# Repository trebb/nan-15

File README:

NaN-15 -- a 15-key DIY computer keyboard

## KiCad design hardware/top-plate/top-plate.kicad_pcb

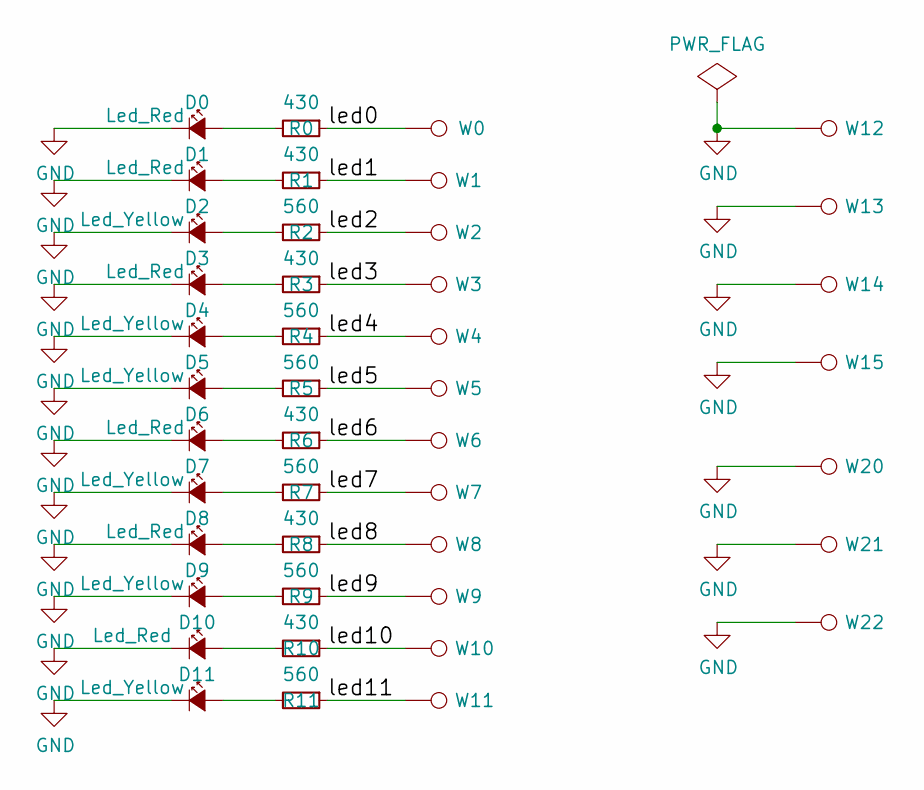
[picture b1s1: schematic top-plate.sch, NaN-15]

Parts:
D0, D1, D3, D6, D8, D10: Led_Red; LED_1206_REVERSE
D2, D4, D5, D7, D9, D11: Led_Yellow; LED_1206_REVERSE
R0, R1, R3, R6, R8, R10: 430; R_1206
R2, R4, R5, R7, R9, R11: 560; R_1206
W0, W1, W2, W3, W4, W5, W6, W7, W8, W9, W10, W11, W12, W13, W14, W15: TEST_1P; SolderWirePad_2mm_1-2mmDrill_no_legend
W20, W21, W22: TEST_1P; MountingHole_2.2mm_M2_Pad

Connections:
/led0: R0.1, W0.1
/led1: R1.1, W1.1
/led2: R2.1, W2.1
/led3: R3.1, W3.1
/led4: R4.1, W4.1
/led5: R5.1, W5.1
/led6: R6.1, W6.1
/led7: R7.1, W7.1
/led8: R8.1, W8.1
/led9: R9.1, W9.1
/led10: R10.1, W10.1
/led11: R11.1, W11.1
GND: D0.1 (K), D1.1 (K), D2.1 (K), D3.1 (K), D4.1 (K), D5.1 (K), D6.1 (K), D7.1 (K), D8.1 (K), D9.1 (K), D10.1 (K), D11.1 (K), W12.1, W13.1, W14.1, W15.1, W20.1, W21.1, W22.1
unnamed: D0.2 (A), R0.2
unnamed: D1.2 (A), R1.2
unnamed: D2.2 (A), R2.2
unnamed: D3.2 (A), R3.2
unnamed: D4.2 (A), R4.2
unnamed: D5.2 (A), R5.2
unnamed: D6.2 (A), R6.2
unnamed: D7.2 (A), R7.2
unnamed: D8.2 (A), R8.2
unnamed: D9.2 (A), R9.2
unnamed: D10.2 (A), R10.2
unnamed: D11.2 (A), R11.2

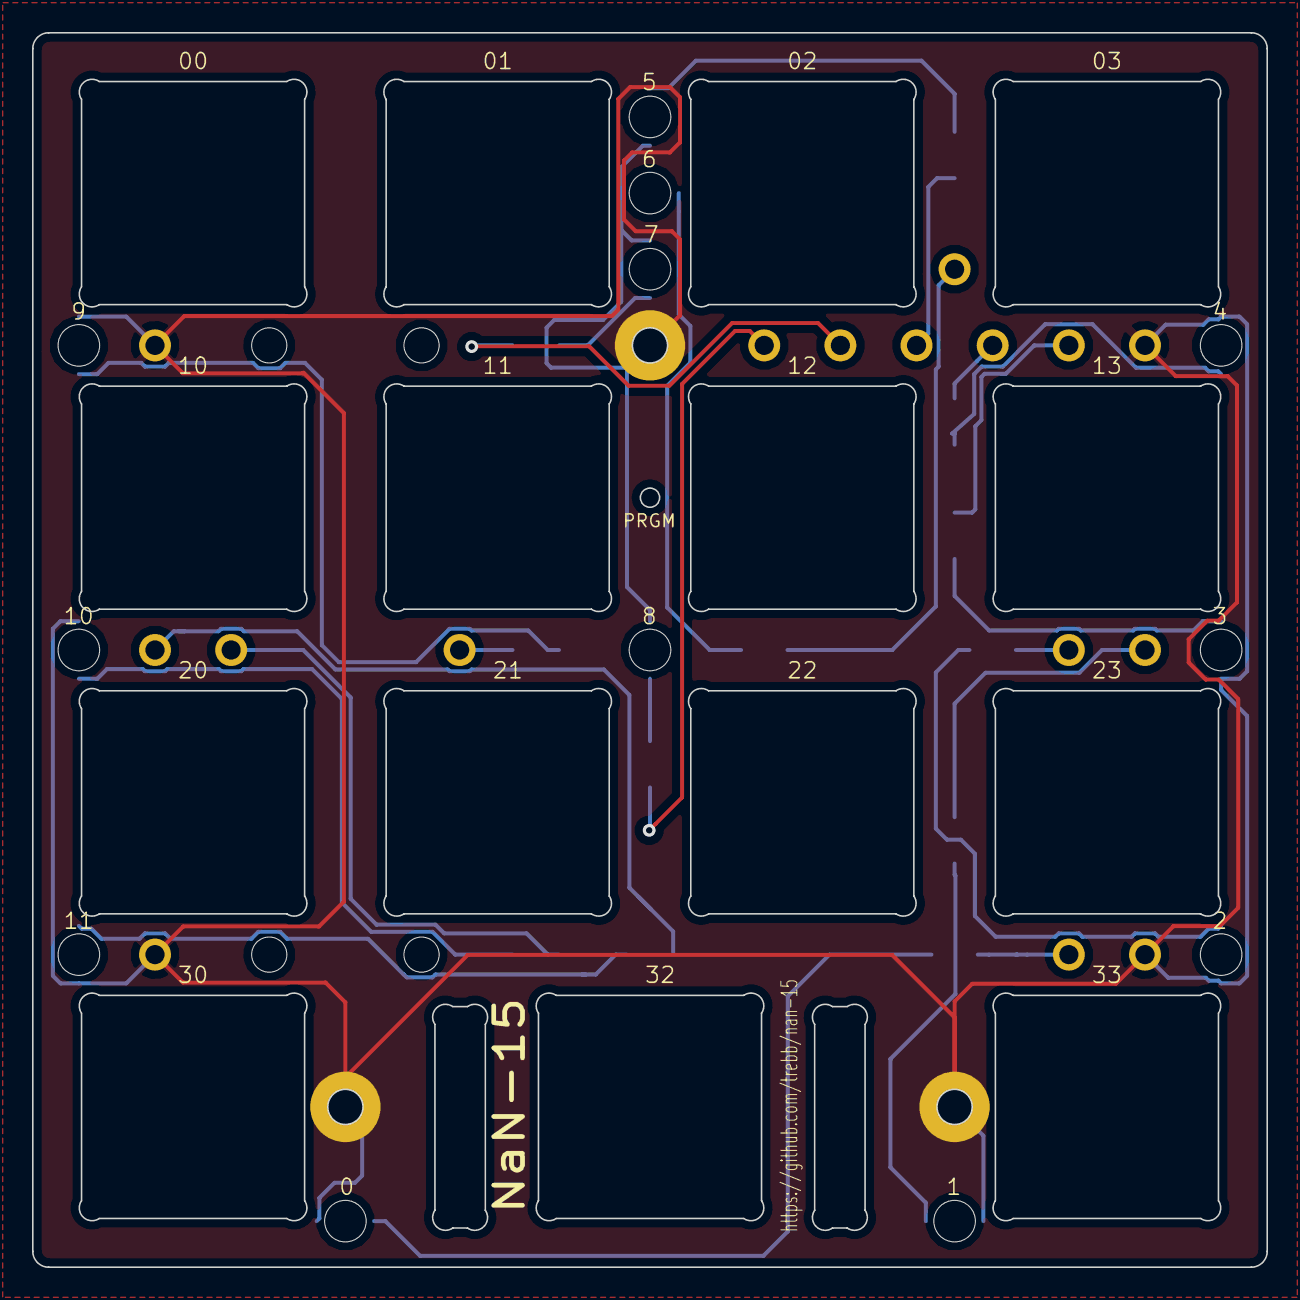
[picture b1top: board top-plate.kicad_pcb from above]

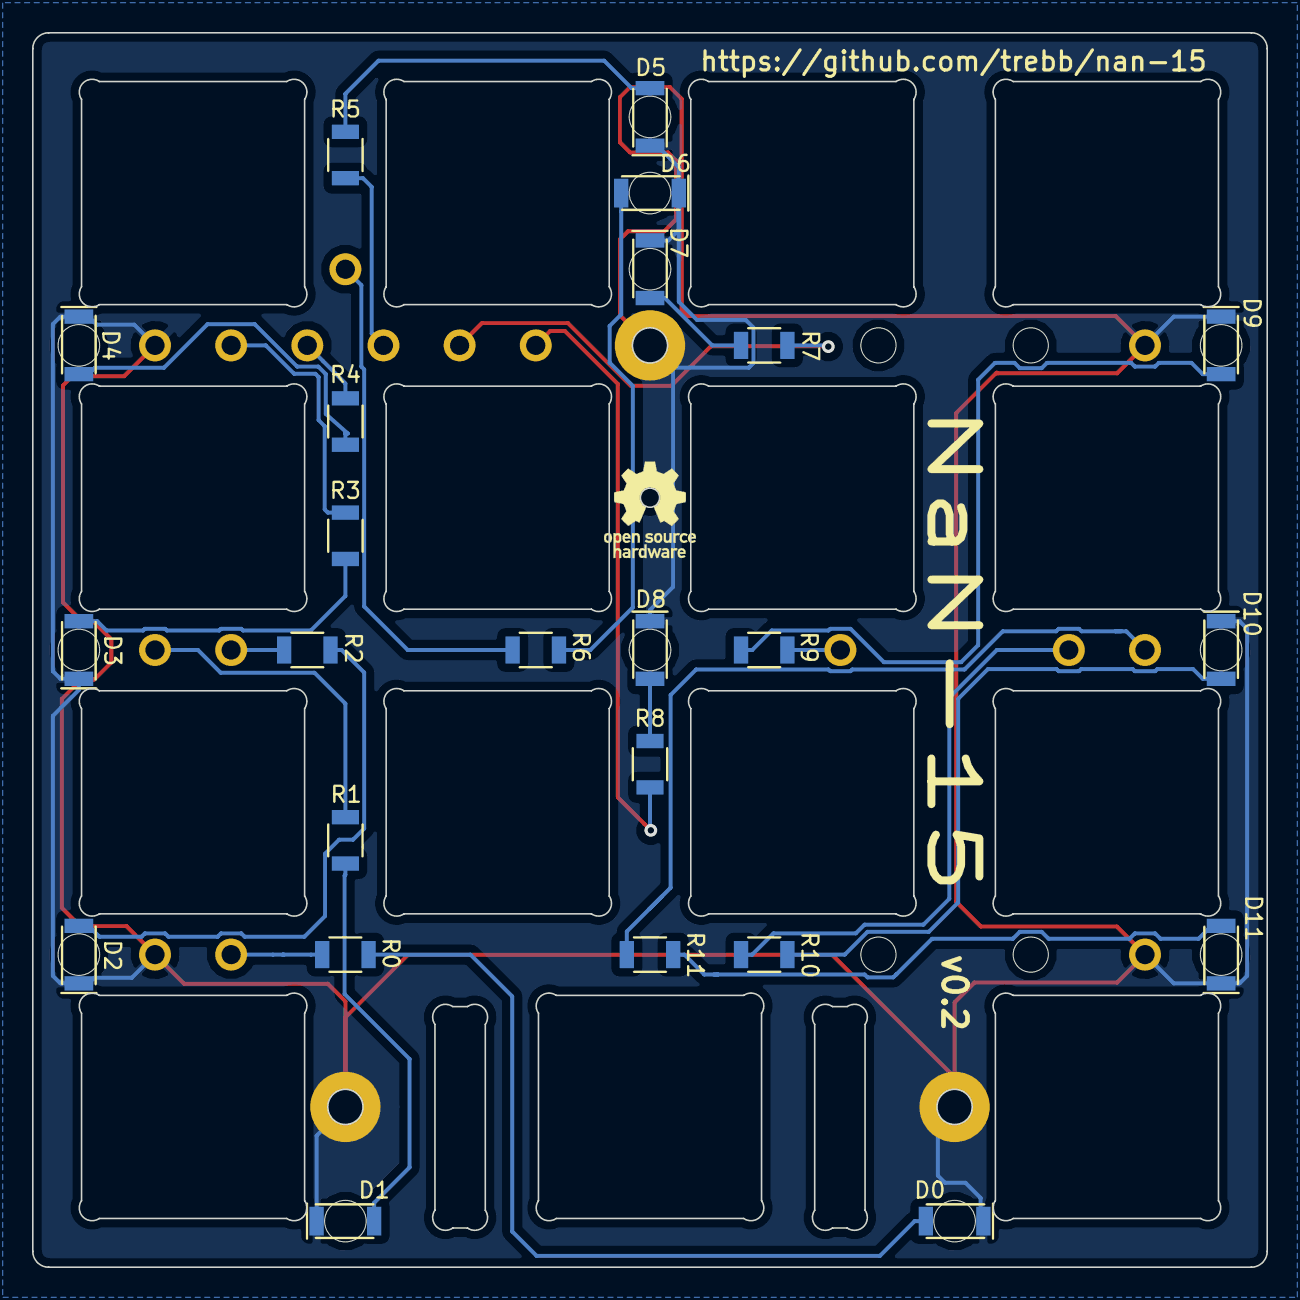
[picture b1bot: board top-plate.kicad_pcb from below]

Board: 2 copper layers, 77.2 x 77.2 mm, 47 parts (24 on the bottom side), 25 nets.

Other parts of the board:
HS4, HS5, HS6, HS7: HEATSINK; MountingHole_2.2mm_M2

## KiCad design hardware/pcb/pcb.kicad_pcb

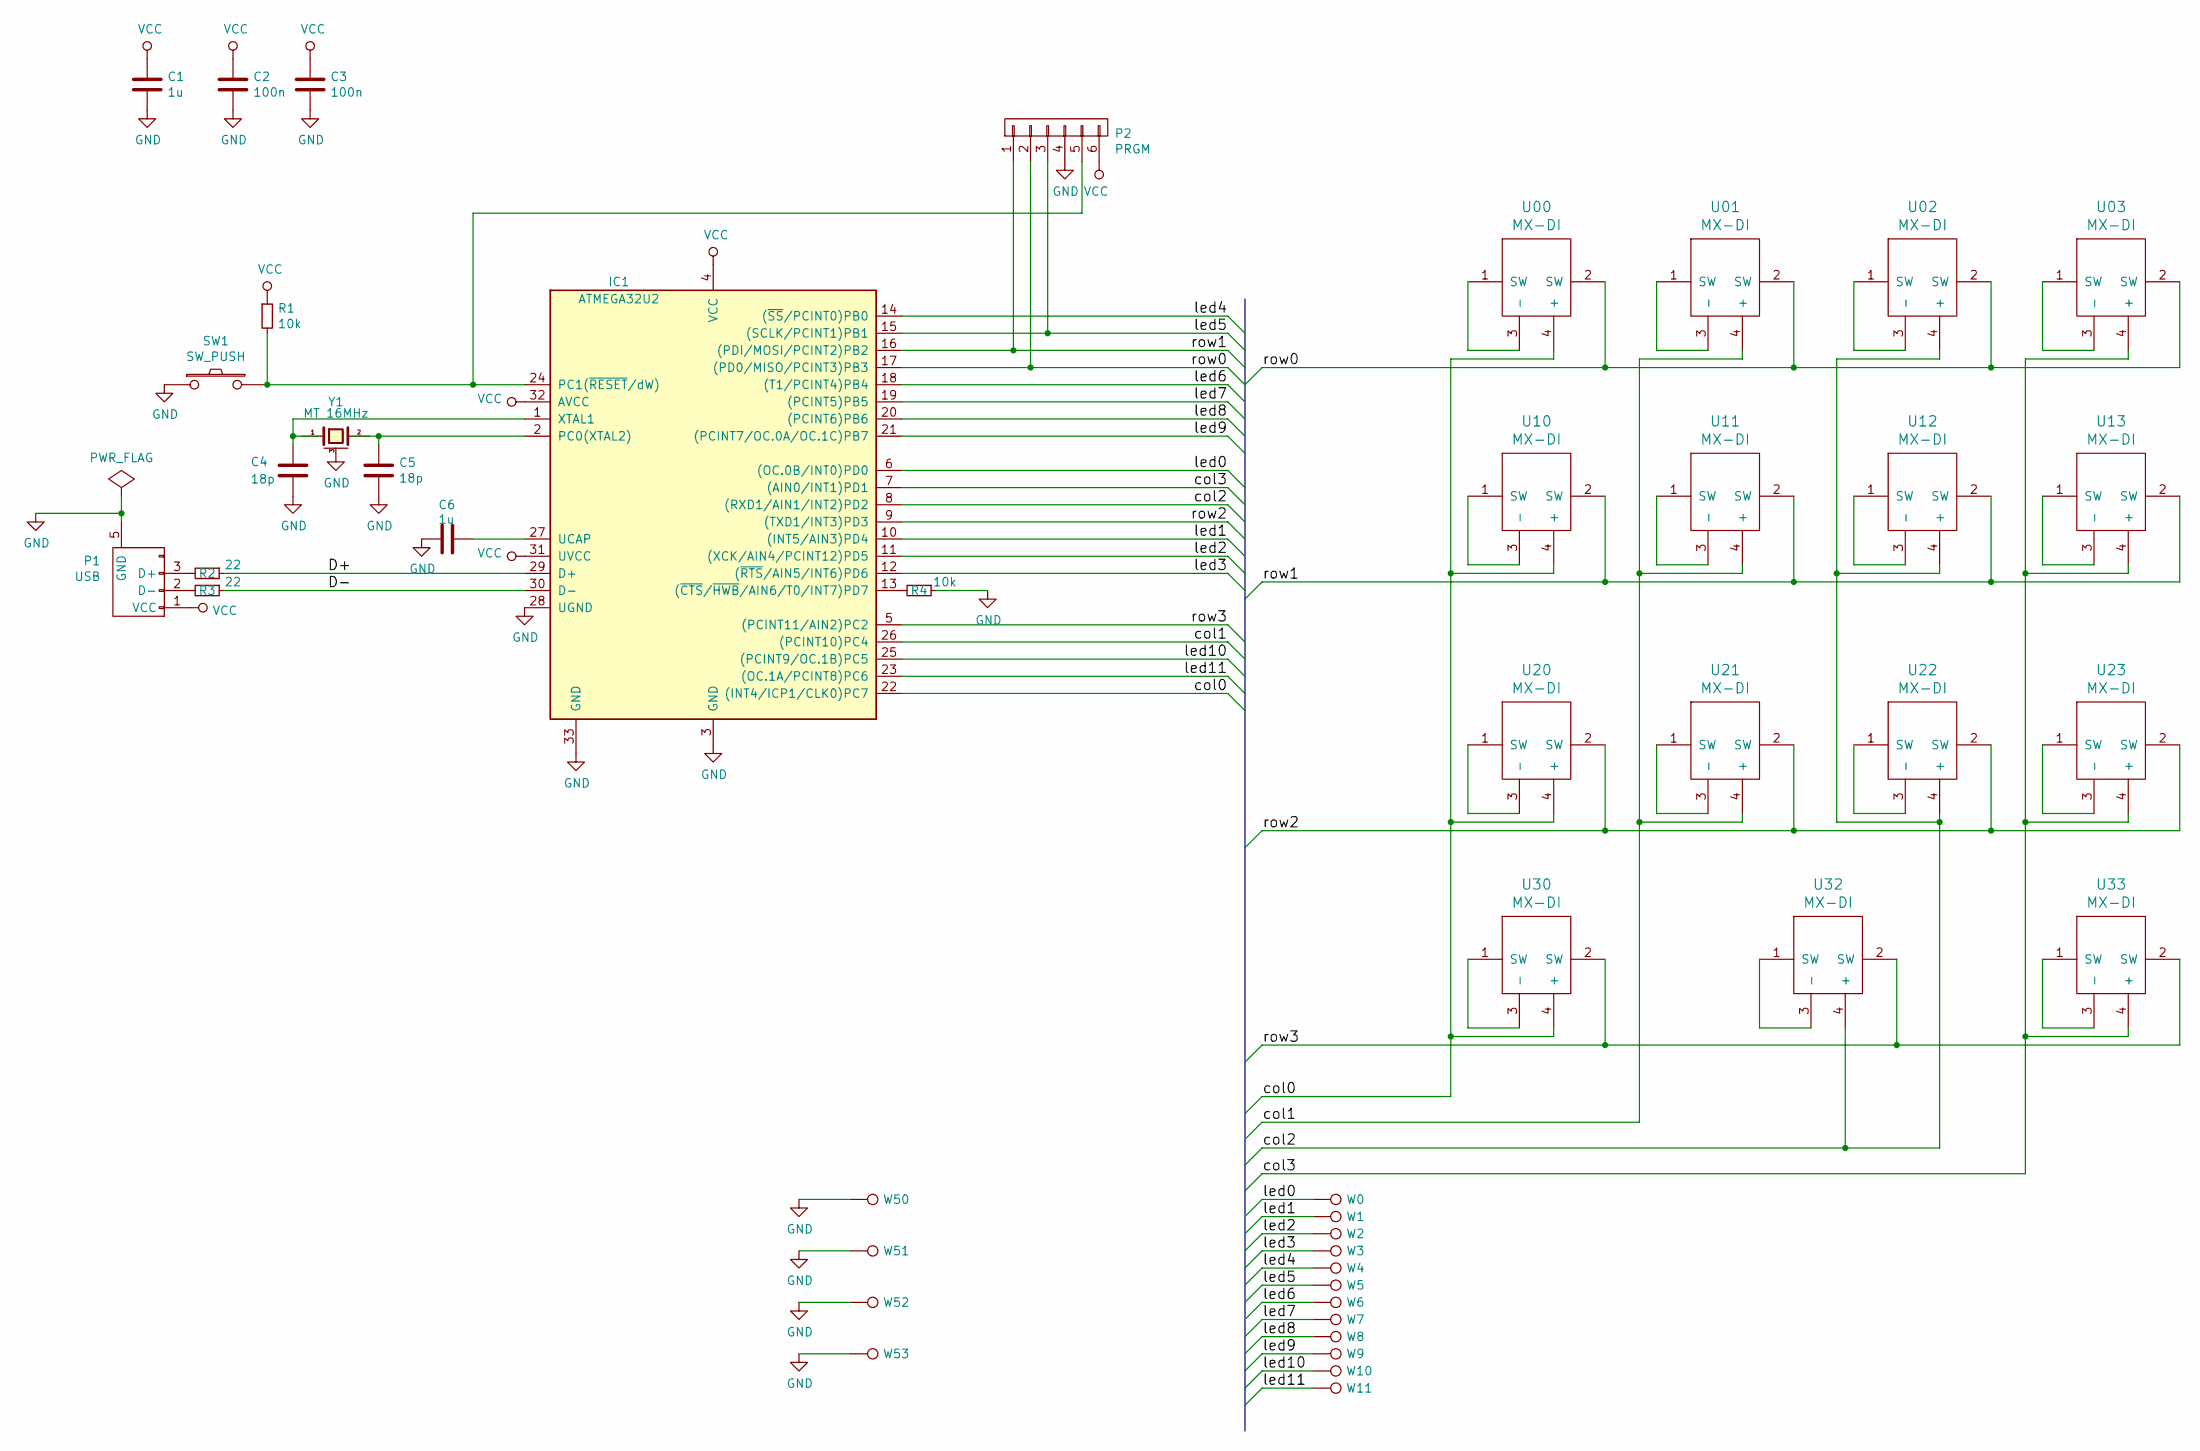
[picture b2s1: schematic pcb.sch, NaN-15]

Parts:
C1, C6: 1u; C_1206
C2, C3: 100n; C_1206
C4, C5: 18p; C_1206
IC1: ATMEGA32U2; QFN-32-1EP_5x5mm_Pitch0.5mm
P1: USB; SolderWirePad_4xInline_1mmDrill
P2: PRGM; Program_1x06
R1, R4: 10k; R_1206
R2, R3: 22; R_1206
SW1: SW_PUSH; button_3x6_smd
U00, U01, U02, U03, U10, U11, U12, U13, U20, U21, U22, U23, U30, U32, U33: MX-DI; MXDIODE
W0, W1, W2, W3, W4, W5, W6, W7, W8, W9, W10, W11, W50, W51, W52, W53: TEST_1P; SolderWirePad_2mm_1-2mmDrill_no_legend
Y1: MT 16MHz; crystal_MT_32x25

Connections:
/D+: IC1.29 (D+), R2.1
/D-: IC1.30 (D-), R3.1
/col0: IC1.22 ((INT4/ICP1/CLK0)PC7), U00.4 (+), U10.4 (+), U20.4 (+), U30.4 (+)
/col1: IC1.26 ((PCINT10)PC4), U01.4 (+), U11.4 (+), U21.4 (+)
/col2: IC1.8 ((RXD1/AIN1/INT2)PD2), U02.4 (+), U12.4 (+), U22.4 (+), U32.4 (+)
/col3: IC1.7 ((AIN0/INT1)PD1), U03.4 (+), U13.4 (+), U23.4 (+), U33.4 (+)
/led0: IC1.6 ((OC.0B/INT0)PD0), W0.1
/led1: IC1.10 ((INT5/AIN3)PD4), W1.1
/led2: IC1.11 ((XCK/AIN4/PCINT12)PD5), W2.1
/led3: IC1.12 ((~RTS~/AIN5/INT6)PD6), W3.1
/led4: IC1.14 ((~SS~/PCINT0)PB0), W4.1
/led5: IC1.15 ((SCLK/PCINT1)PB1), P2.3, W5.1
/led6: IC1.18 ((T1/PCINT4)PB4), W6.1
/led7: IC1.19 ((PCINT5)PB5), W7.1
/led8: IC1.20 ((PCINT6)PB6), W8.1
/led9: IC1.21 ((PCINT7/OC.0A/OC.1C)PB7), W9.1
/led10: IC1.25 ((PCINT9/OC.1B)PC5), W10.1
/led11: IC1.23 ((OC.1A/PCINT8)PC6), W11.1
/row0: IC1.17 ((PD0/MISO/PCINT3)PB3), P2.2, U00.2 (SW), U01.2 (SW), U02.2 (SW), U03.2 (SW)
/row1: IC1.16 ((PDI/MOSI/PCINT2)PB2), P2.1, U10.2 (SW), U11.2 (SW), U12.2 (SW), U13.2 (SW)
/row2: IC1.9 ((TXD1/INT3)PD3), U20.2 (SW), U21.2 (SW), U22.2 (SW), U23.2 (SW)
/row3: IC1.5 ((PCINT11/AIN2)PC2), U30.2 (SW), U32.2 (SW), U33.2 (SW)
GND: C1.2, C2.2, C3.2, C4.2, C5.2, C6.1, IC1.3 (GND), IC1.28 (UGND), IC1.33 (GND), P1.5 (GND), P2.4, R4.1, SW1.1, W50.1, W51.1, W52.1, W53.1, Y1.3 (case)
unnamed: C4.1, IC1.1 (XTAL1)
unnamed: C5.1, IC1.2 (PC0(XTAL2))
unnamed: C6.2, IC1.27 (UCAP)
unnamed: IC1.13 ((~CTS~/~HWB~/AIN6/T0/INT7)PD7), R4.2
unnamed: IC1.24 (PC1(~RESET~/dW)), P2.5, R1.2, SW1.2
unnamed: P1.2 (D-), R3.2
unnamed: P1.3 (D+), R2.2
unnamed: U00.1 (SW), U00.3 (-)
unnamed: U01.1 (SW), U01.3 (-)
unnamed: U02.1 (SW), U02.3 (-)
unnamed: U03.1 (SW), U03.3 (-)
unnamed: U10.1 (SW), U10.3 (-)
unnamed: U11.1 (SW), U11.3 (-)
unnamed: U12.1 (SW), U12.3 (-)
unnamed: U13.1 (SW), U13.3 (-)
unnamed: U20.1 (SW), U20.3 (-)
unnamed: U21.1 (SW), U21.3 (-)
unnamed: U22.1 (SW), U22.3 (-)
unnamed: U23.1 (SW), U23.3 (-)
unnamed: U30.1 (SW), U30.3 (-)
unnamed: U32.1 (SW), U32.3 (-)
unnamed: U33.1 (SW), U33.3 (-)
VCC: C1.1, C2.1, C3.1, IC1.4 (VCC), IC1.31 (UVCC), IC1.32 (AVCC), P1.1 (VCC), P2.6, R1.1

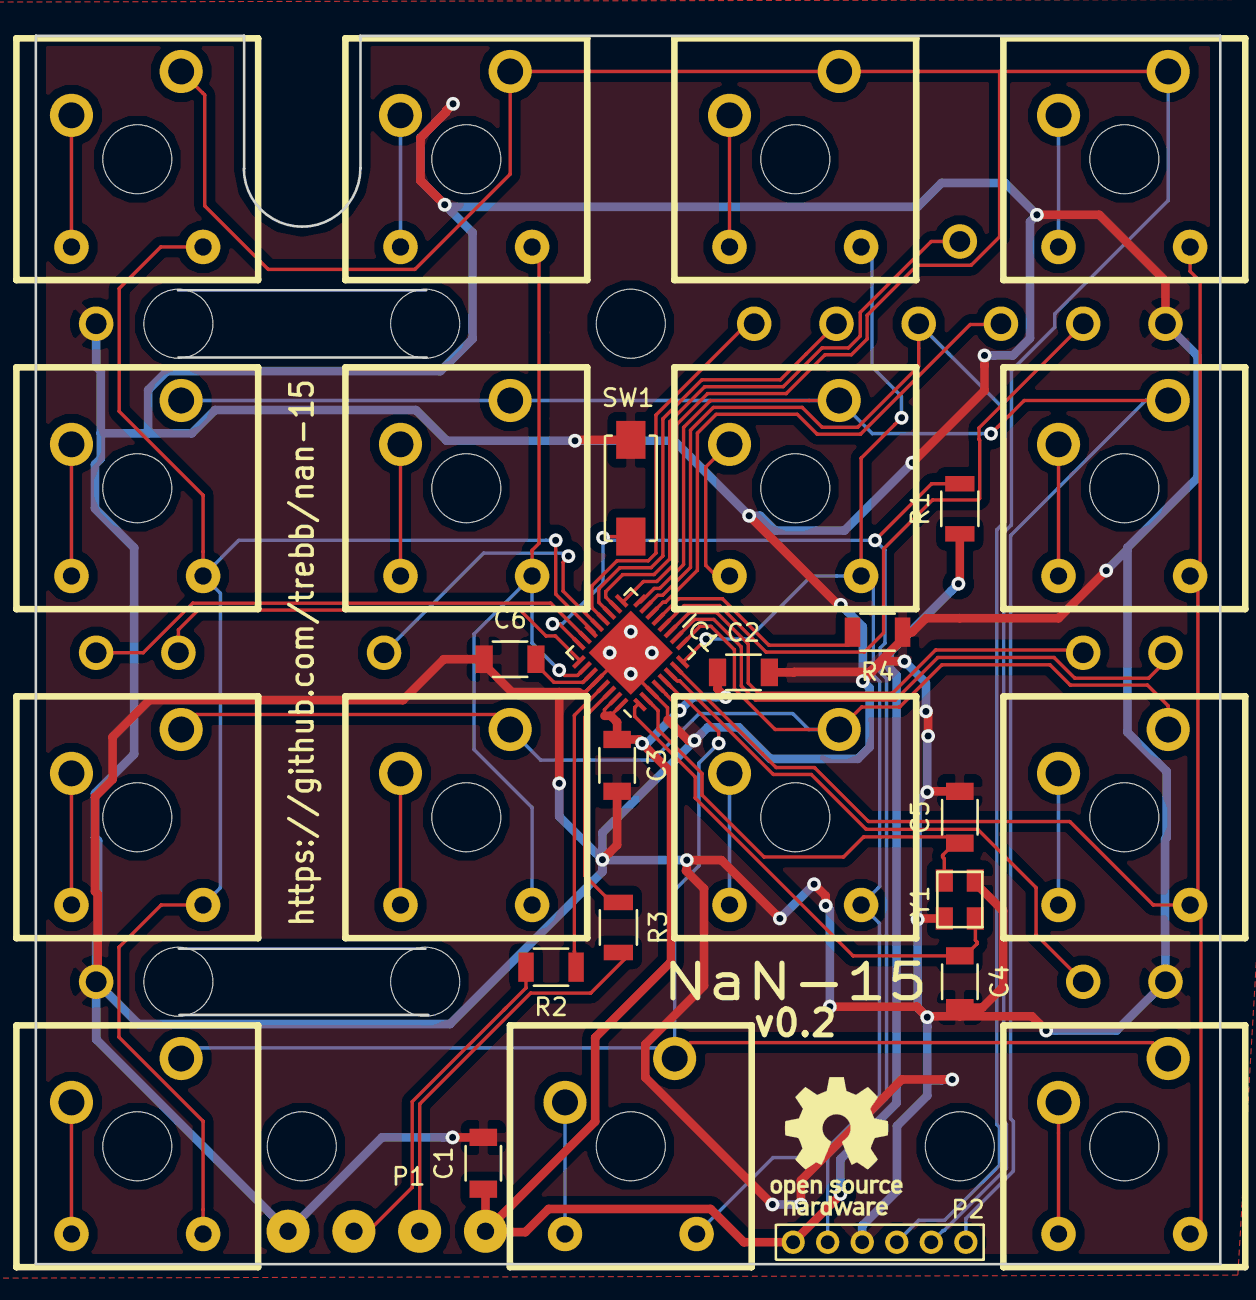
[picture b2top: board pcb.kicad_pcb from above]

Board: 2 copper layers, 68.6 x 71.1 mm, 54 parts (1 on the bottom side), 46 nets.

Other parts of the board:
HS1, HS2, HS3, HS4, HS5, HS6, HS7: HEATSINK; Plain_Hole_4mm
OSHW: OSHW-Logo_28.5x30mm_SilkScreen

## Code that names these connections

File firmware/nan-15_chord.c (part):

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/*
 * Keychords comprising one key per column on the upper three rows
 */
#define CHRD(COL0, COL1, COL2, COL3) ((COL0)<<6 | (COL1)<<4 | (COL2)<<2 | (COL3))
#define KEYPAIR(LOWER_MODS, LOWER_CODE, UPPER_MODS, UPPER_CODE) \
    {.mods_lo = (LOWER_MODS), .code_lo = (KC_##LOWER_CODE), \
            .mods_up = (UPPER_MODS), .code_up = (KC_##UPPER_CODE)}
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
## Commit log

2016-11-14 Add PCB
2016-11-14 Add DXF file of top plate
2016-11-14 Add .gitignore
2016-11-16 Make pads of the QFN32 PDB footprint longer
2016-11-16 Various PCB edits
2016-11-16 Design a top plate
2016-11-16 Design a bottom plate
2016-11-18 Connect all PWM pins to LEDs; show PCB version number
2016-11-19 Add 3D-printable frame
2016-11-19 Print switch numbers onto top plate
2016-11-19 Minor PCB edits regarding Gerber output
2016-11-19 Add a bottom label
2016-11-19 Add administrative stuff
2016-11-22 Add untested firmware
2016-12-07 Update version numbers on PCB silkscreens
2016-12-13 Reduce depth of LED cutouts in frame
2016-12-26 Implement simplistic firmware for testing hardware
2017-02-09 Add code to build and install a bootloader
2017-02-21 Firmware build process cleanup
2017-02-26 Prune test firmware
2017-03-03 Add firmware for chorded operation
2017-03-05 Add support for LEDs and modifiers
2017-03-07 Add make target that creates a cflow call graph
2017-03-07 Line-wrap the cflow call graph
2017-03-09 Fix cflow issue
2017-03-11 Prune matrix.c
2017-03-17 Improve chorded firmware
    - Editable chordmaps, stored in EEPROM
    - One-shot and toggled modifiers
    - Chordmap printing
    - Additional non-chorded layers
2017-03-25 Add support for EEPROM-stored macros
2017-03-25 Add a list of hardware bugs
2017-03-26 Tweak printing output and chordmap
2017-03-28 Rearrange LED code to facilitate documentation
2017-04-14 Add chordmap cheatsheet building program
2017-05-27 Edit firmware source to make documentation extraction easier
2017-05-27 Improve chordmap SVG creation
2017-05-28 Add LED cheatsheet generator
2017-05-28 Add forgotten KiCad files
2017-05-28 Add a bunch of .gitignore files
2017-05-28 Add cheatsheet generator documentation
2017-05-28 Fix bug in chordmap printing
    In second or later output attempt, the first line got mangled.
2017-05-28 Prune legacy/unusual keycodes from chordmap
2017-05-28 Put more (i.e. all) keycodes into chordmap cheatsheet
2017-05-28 Cheatsheet formatting; exclude the empty chord
2017-06-04 Chordmap cheatsheet: add a chord awkwardness score
2017-06-04 Rearrange default chordmap
2017-06-04 Modify cheatsheet color scheme
2017-06-05 Chordmap cheatsheet: tweak style; add legend for awkwardness score
2017-06-09 Include missing shift-only chord in cheatsheet
2017-06-09 Fix README staleness
2017-06-09 Get rid of explicit Right Alt/AltGr modifiers
2017-06-09 Change default chordmap
2017-06-09 Emit toggled modifiers immediately
    This is useful for modified mouse activity and for getting out of
    screen savers.
2017-06-09 Make layer-changing chords distinguishable
2017-06-09 Create version-dependent git tags
2017-06-09 CC14 is our official USB PID (issued by pid.codes)
2017-06-10 Modify non-chord keymaps
    They can now also have sublayers.
2017-06-10 Draw a bottom sticker
2017-06-24 Setting fuses isn't required; update README
2017-06-24 README: mention power consumption
2017-06-24 Swap left/right arrows in default chordmap
2017-06-24 Typo
2017-06-24 Edit bottom sticker
2017-06-24 gh-pages pseudo commit
2017-06-27 README: include another image
2017-06-29 Bugfix: Ctrl had the wrong LEDs flash

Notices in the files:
firmware/nan-15_chord.c:
Copyright 2013,2016 Jun Wako <wakojun@gmail.com>
Copyright 2017 Bert Burgemeister <trebbu@googlemail.com>
This program is free software: you can redistribute it and/or modify
it under the terms of the GNU General Public License as published by
the Free Software Foundation, either version 2 of the License, or
(at your option) any later version.
